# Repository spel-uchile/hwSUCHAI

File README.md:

hwSUCHAI
========

PCB, antennas, 3D models, and other parts of the Cubesat SUCHAI.

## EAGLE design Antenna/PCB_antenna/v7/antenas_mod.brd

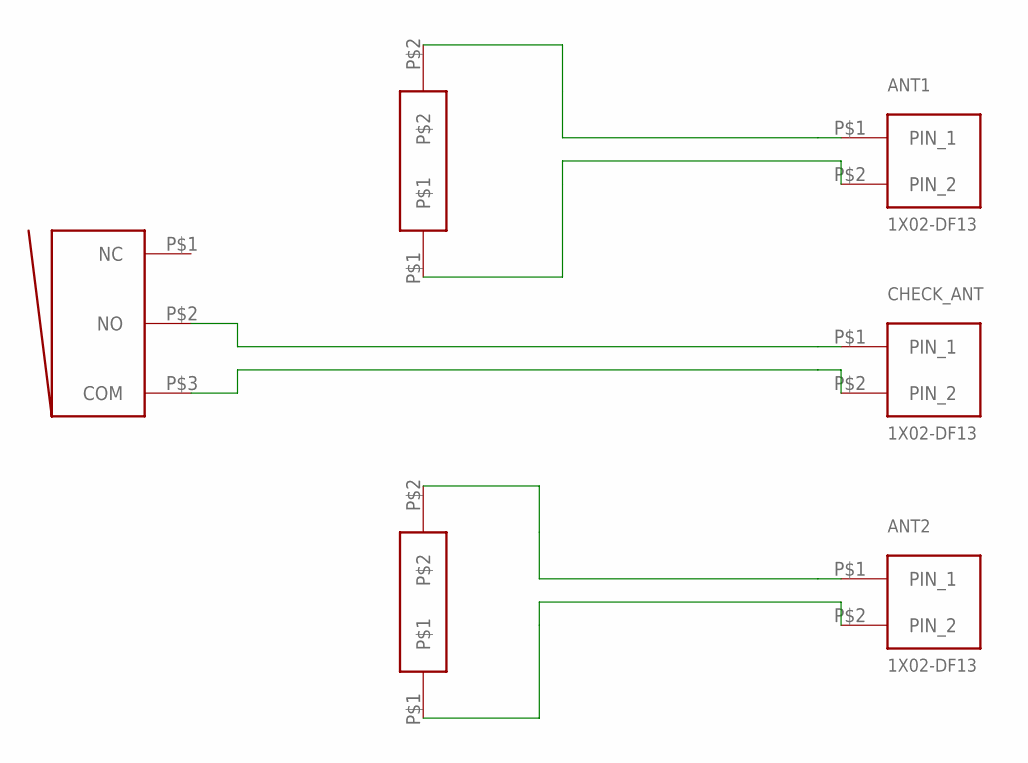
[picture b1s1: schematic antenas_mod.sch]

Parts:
ANT1, ANT2: 1X02-DF13; DF-13
CHECK_ANT: 1X02-DF13; DF-13
U$1: SWITCH_ANT_TRHU; 3_HOLE
U$5, U$6: RPOWER

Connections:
COM: CHECK_ANT.P$2 (PIN_2), U$1.P$3 (COM)
unnamed: ANT1.P$1 (PIN_1), U$5.P$2
unnamed: ANT1.P$2 (PIN_2), U$5.P$1
unnamed: ANT2.P$1 (PIN_1), U$6.P$2
unnamed: ANT2.P$2 (PIN_2), U$6.P$1
NO: CHECK_ANT.P$1 (PIN_1), U$1.P$2 (NO)

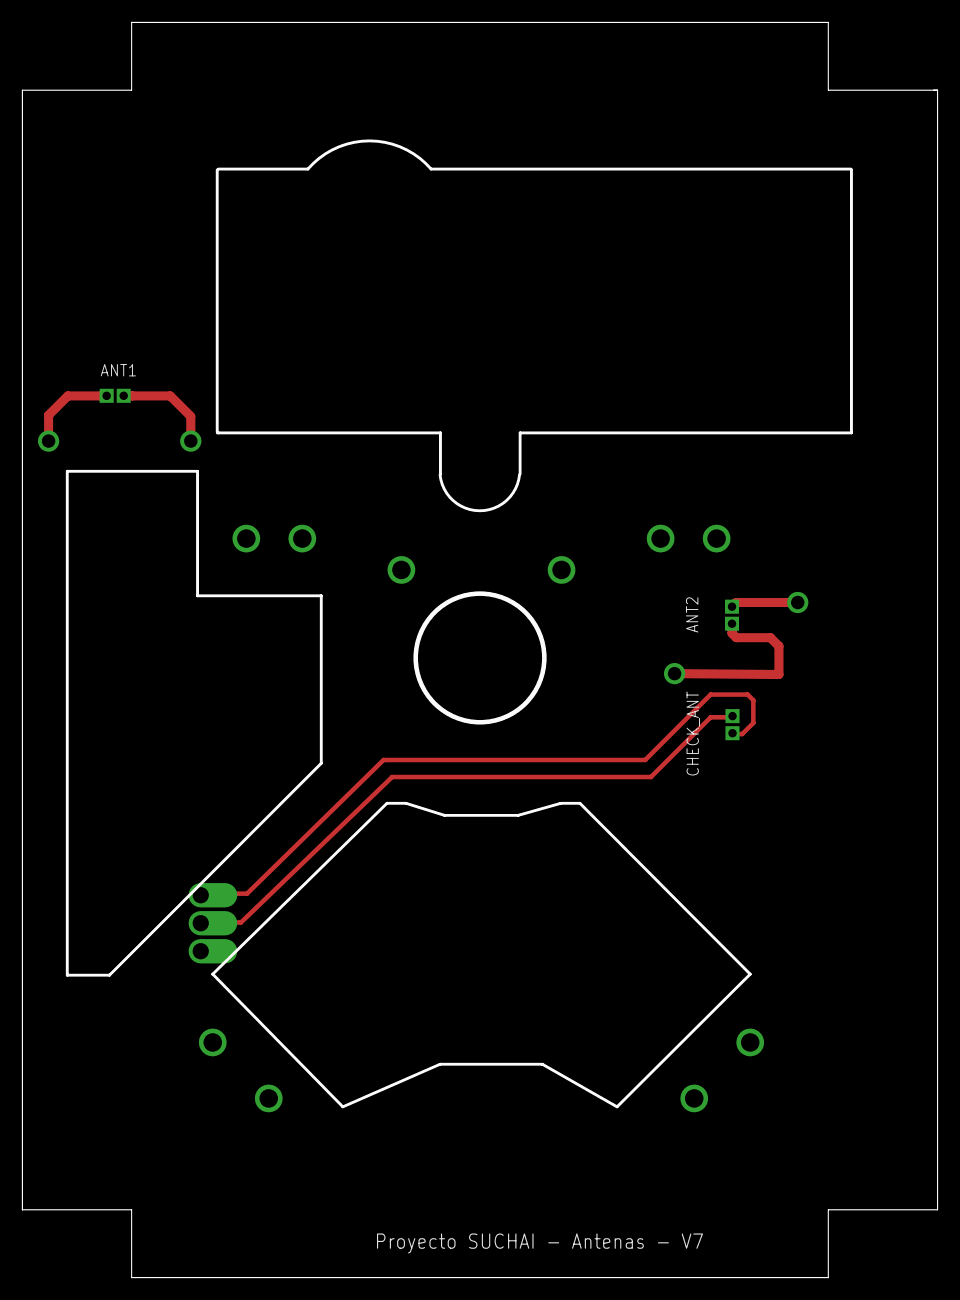
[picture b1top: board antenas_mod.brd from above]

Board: 2 copper layers, 81.7 x 112.1 mm, 6 parts (1 on the bottom side), 6 nets.

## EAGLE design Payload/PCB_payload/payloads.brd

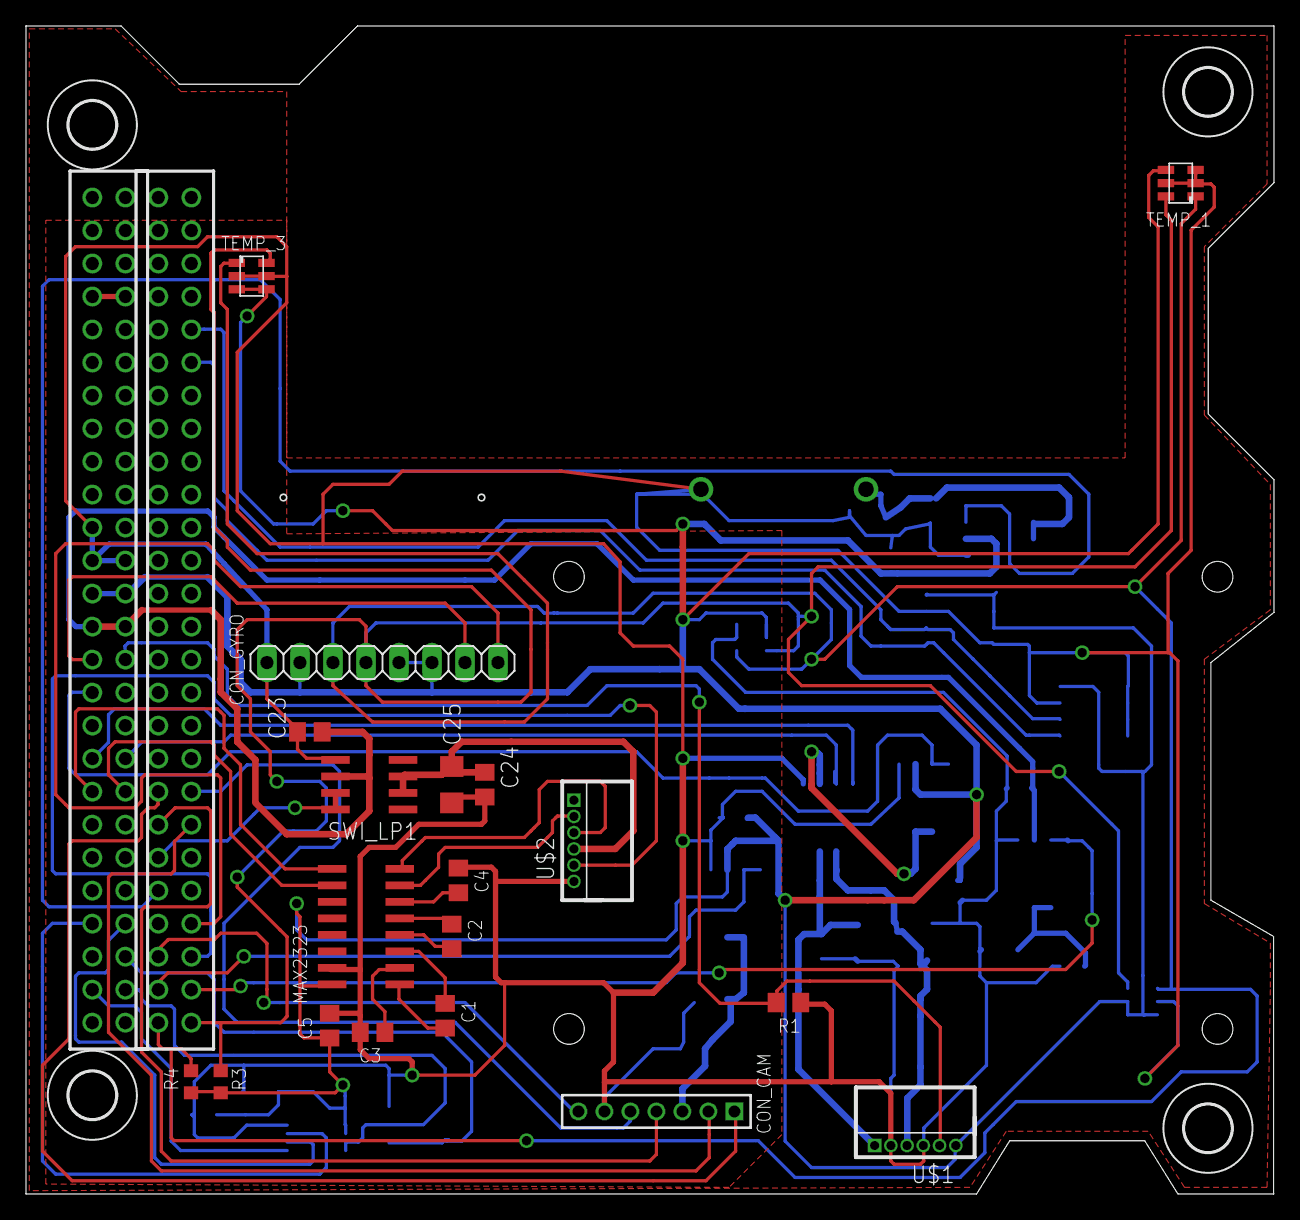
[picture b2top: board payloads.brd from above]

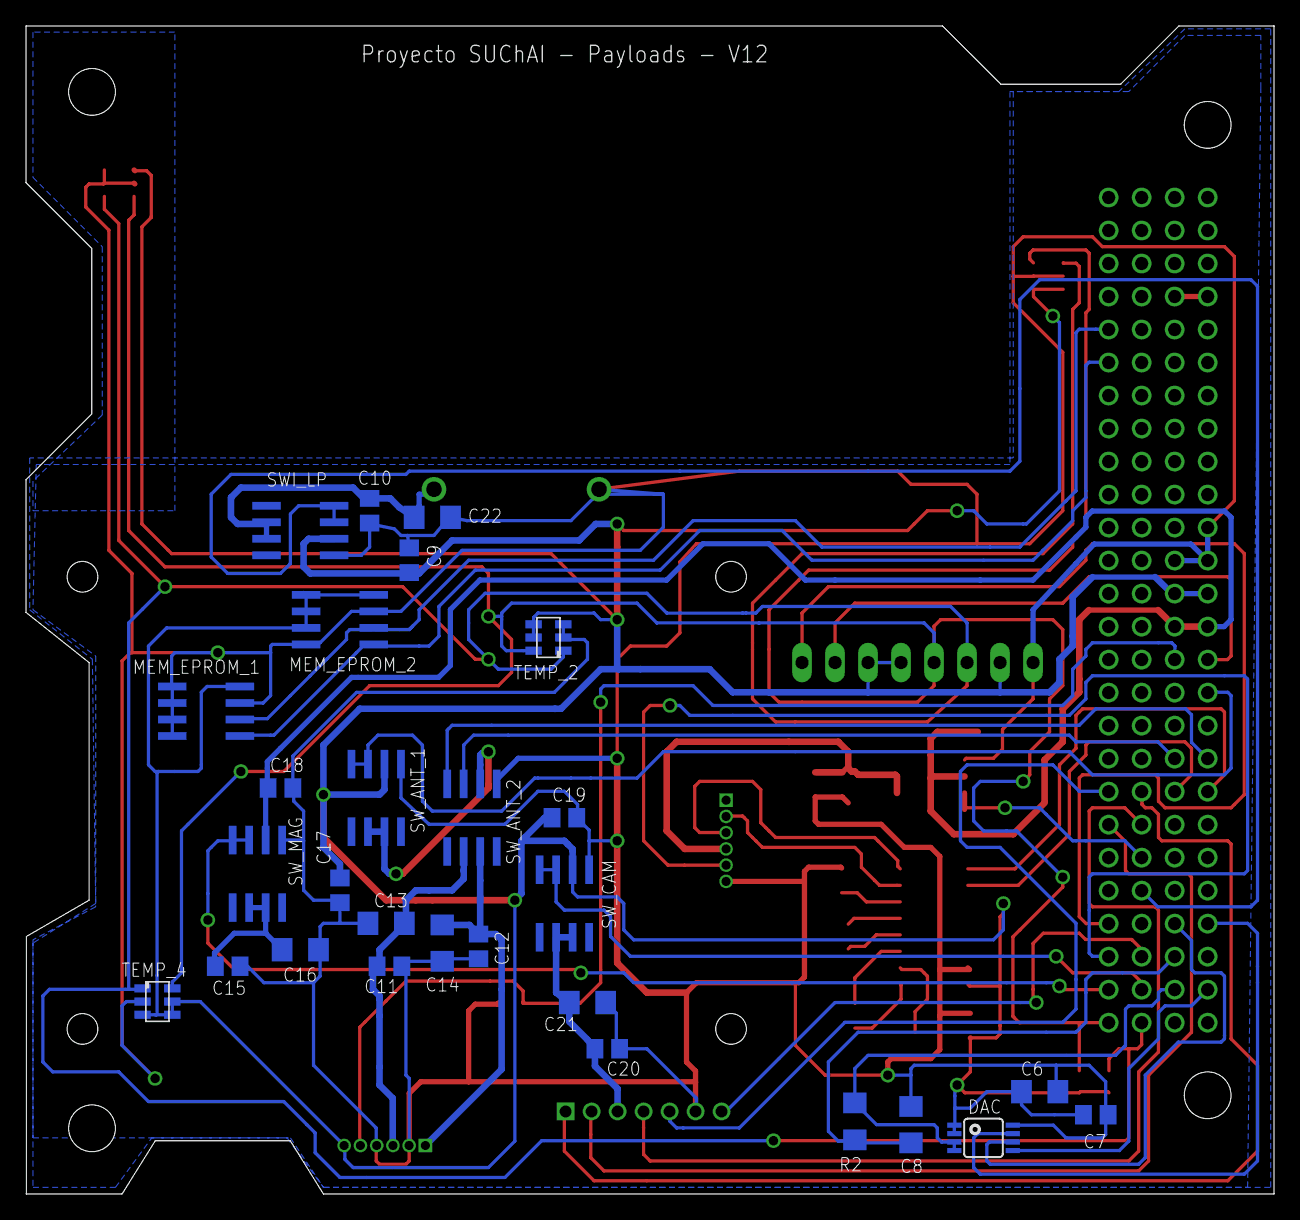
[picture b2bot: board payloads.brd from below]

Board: 2 copper layers, 96.0 x 89.9 mm, 53 parts (28 on the bottom side), 46 nets.

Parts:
C1, C2, C3, C4, C5, C9, C10, C11, C12, C15, C17, C18, C19, C20, C23, C24: 0.1uf; C0805
C6: 10u; C1206
C7: 0.1u; C0805
C8: 1u; C1206
C13, C14, C16, C21, C22, C25: 22uf; C1206
CON_CAM: CAM_CON; 1X07-2P
CON_GYRO: GYRO_TRI_CON; 1X08
DAC: DAC8851; MSOP8
H1H2: PC104_CONN; PC_104
MAX2323: MAX3232_S; SOIC16N
MEM_EPROM_1, MEM_EPROM_2: M24C02; SOIC8
R1: 10k; R0805
R2: 1k21; R1206
R3, R4: 10k; R0603
SWI_LP, SWI_LP1: TPS2066DG4; SOIC8
SW_ANT_1, SW_ANT_2: TPS2066DG4; SOIC8
SW_CAM: TPS2066DG4; SOIC8
SW_MAG: TPS2066DG4; SOIC8
TEMP_1, TEMP_2, TEMP_3, TEMP_4: TMP100; SOT23-6
U$1, U$2: DF13-6P-1.25DS
U$3: RPOWER
U$11, U$12, U$13, U$14: 3,6

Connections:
3V3: C5.1, C6.1, C7.1, C9.1, C17.1, C19.1, CON_GYRO.2, CON_GYRO.5, CON_GYRO.6, DAC.1, DAC.2, H1H2.79, H1H2.80, MAX2323.16, MEM_EPROM_1.8, MEM_EPROM_2.1, MEM_EPROM_2.2, MEM_EPROM_2.3, MEM_EPROM_2.8, R3.2, R4.2, SWI_LP.2, SW_ANT_1.2, SW_CAM.2, TEMP_1.4, TEMP_2.4, TEMP_2.5, TEMP_3.3, TEMP_3.4, TEMP_4.3, TEMP_4.4, TEMP_4.5, U$1.P$6
5V0: C18.1, C23.1, H1H2.77, H1H2.78, SWI_LP1.2, SW_MAG.2
ANT1: C12.1, C14.1, SW_ANT_2.7, U$1.P$1
ANT1_SW2: H1H2.69, SW_ANT_2.3
ANT2: C11.1, C13.1, SW_ANT_2.6, U$1.P$3
ANT2_SW2: H1H2.70, SW_ANT_2.4
ANT12_SW1: H1H2.74, SW_ANT_1.3, SW_ANT_1.4
CAM_CLK: CON_CAM.2, H1H2.13
CAM_CS: CON_CAM.1, H1H2.16
CAM_HOLD: CON_CAM.7, H1H2.6
CAM_MISO: CON_CAM.4, H1H2.14
CAM_MOSI: CON_CAM.5, H1H2.15
CAM_SW: H1H2.4, SW_CAM.3, SW_CAM.4
CAM_VIN: C20.1, C21.1, CON_CAM.3, SW_CAM.6, SW_CAM.7
CHECK_ANT: H1H2.75, R1.2, U$1.P$5
GND: C3.2, C4.2, C5.2, C6.2, C7.2, C8.2, C9.2, C10.2, C11.2, C12.2, C13.2, C14.2, C15.2, C16.2, C17.2, C18.2, C19.2, C20.2, C21.2, C22.2, C23.2, C24.2, C25.2, CON_CAM.6, CON_GYRO.1, DAC.8, H1H2.81, H1H2.82, H1H2.84, MAX2323.15, MEM_EPROM_1.1, MEM_EPROM_1.2, MEM_EPROM_1.3, MEM_EPROM_1.4, MEM_EPROM_1.7, MEM_EPROM_2.4, MEM_EPROM_2.7, R1.1, SWI_LP.1, SWI_LP1.1, SW_ANT_1.1, SW_ANT_2.1, SW_CAM.1, SW_MAG.1, TEMP_1.2, TEMP_1.3, TEMP_1.5, TEMP_2.2, TEMP_2.3, TEMP_3.2, TEMP_3.5, TEMP_4.2, U$1.P$2, U$1.P$4, U$2.P$6, U$3.P$1
GPS_RESET: H1H2.5, U$2.P$5
GPS_SW: H1H2.12, SWI_LP1.3, SWI_LP1.4
GYRO_INT1: CON_GYRO.8, H1H2.7
GYRO_INT2: CON_GYRO.7, H1H2.76
I2C_SCL: H1H2.43, MEM_EPROM_1.6, MEM_EPROM_2.6
I2C_SDA: H1H2.41, MEM_EPROM_1.5, MEM_EPROM_2.5
LP: C10.1, C22.1, SWI_LP.6, SWI_LP.7, U$3.P$2
MAGN: C15.1, C16.1, SW_MAG.6, SW_MAG.7
MAGN_SW: H1H2.3, SW_MAG.3, SW_MAG.4
unnamed: C1.1, MAX2323.1
unnamed: C1.2, MAX2323.3
unnamed: C2.1, MAX2323.4
unnamed: C2.2, MAX2323.5
unnamed: C3.1, MAX2323.2
unnamed: C4.1, MAX2323.6
OUT1_GPS: C24.1, C25.1, SWI_LP1.6, SWI_LP1.7, U$2.P$4
OUT_IN: SW_ANT_1.6, SW_ANT_1.7, SW_ANT_2.2
PHY_-SYNC: DAC.5, H1H2.56
PHY_DIN: DAC.7, H1H2.60
PHY_SCLK: DAC.6, H1H2.59
RXDA: MAX2323.7, U$2.P$2
RXDA_GPS: H1H2.68, MAX2323.9
SCL2: CON_GYRO.3, H1H2.2, R4.1, TEMP_1.1, TEMP_2.1, TEMP_3.1, TEMP_4.1
SDA2: CON_GYRO.4, H1H2.1, R3.1, TEMP_1.6, TEMP_2.6, TEMP_3.6, TEMP_4.6
SENS1: DAC.3, DAC.4, H1H2.55, R2.1
SENS2: C8.1, H1H2.57, R2.2
SW_LP: H1H2.10, SWI_LP.3, SWI_LP.4
TXDA: MAX2323.8, U$2.P$3
TXDA_GPS: H1H2.67, MAX2323.10
VBATT: H1H2.97, H1H2.98

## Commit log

2014-07-28 se suben archivos de Alex, que contienen los modelos de las placas de antenas (despliegue y balun) y las de el payload (camara-langmuir)
2014-07-28 correcion del ingles
2014-08-18 se agraga doc CDS
2014-08-18 agrego archivo
2014-08-26 se agrega cad del suchai
2014-08-26 se actualizan PARTLIST de placa antenas, balun y payload. Faltan aprox 25% de componentes
2014-08-29 se modifican las placas: antena (acomodar switch en otro lugar y rotar resistencia para mejor amarre, se crea v7 con las modif y v6b sin cambios, se crean gerber), balun (se crean gerber), payload (s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
2014-10-08 se actualizan listas de partes
2015-04-09 se generan versiones para PCB de adaptacion Edison PC104
2015-08-10 se agrega piezas pequeñas de lanzador de langmuir probe
2015-10-08 se agregan datasheet para usarlos de fuene de info para el CAD del SUCHAI
2016-04-01 se crea nueva version de placa para alojar Rasp Zero y Edison. Se parte con arreglar los errores detectados en la parte de Edison
2016-04-07 se corrige bug de ruteo de UART1 y 2
2016-04-11 se declara lista la mita Edison de la placa
2016-04-26 se agrega rapberry zero al PCB
